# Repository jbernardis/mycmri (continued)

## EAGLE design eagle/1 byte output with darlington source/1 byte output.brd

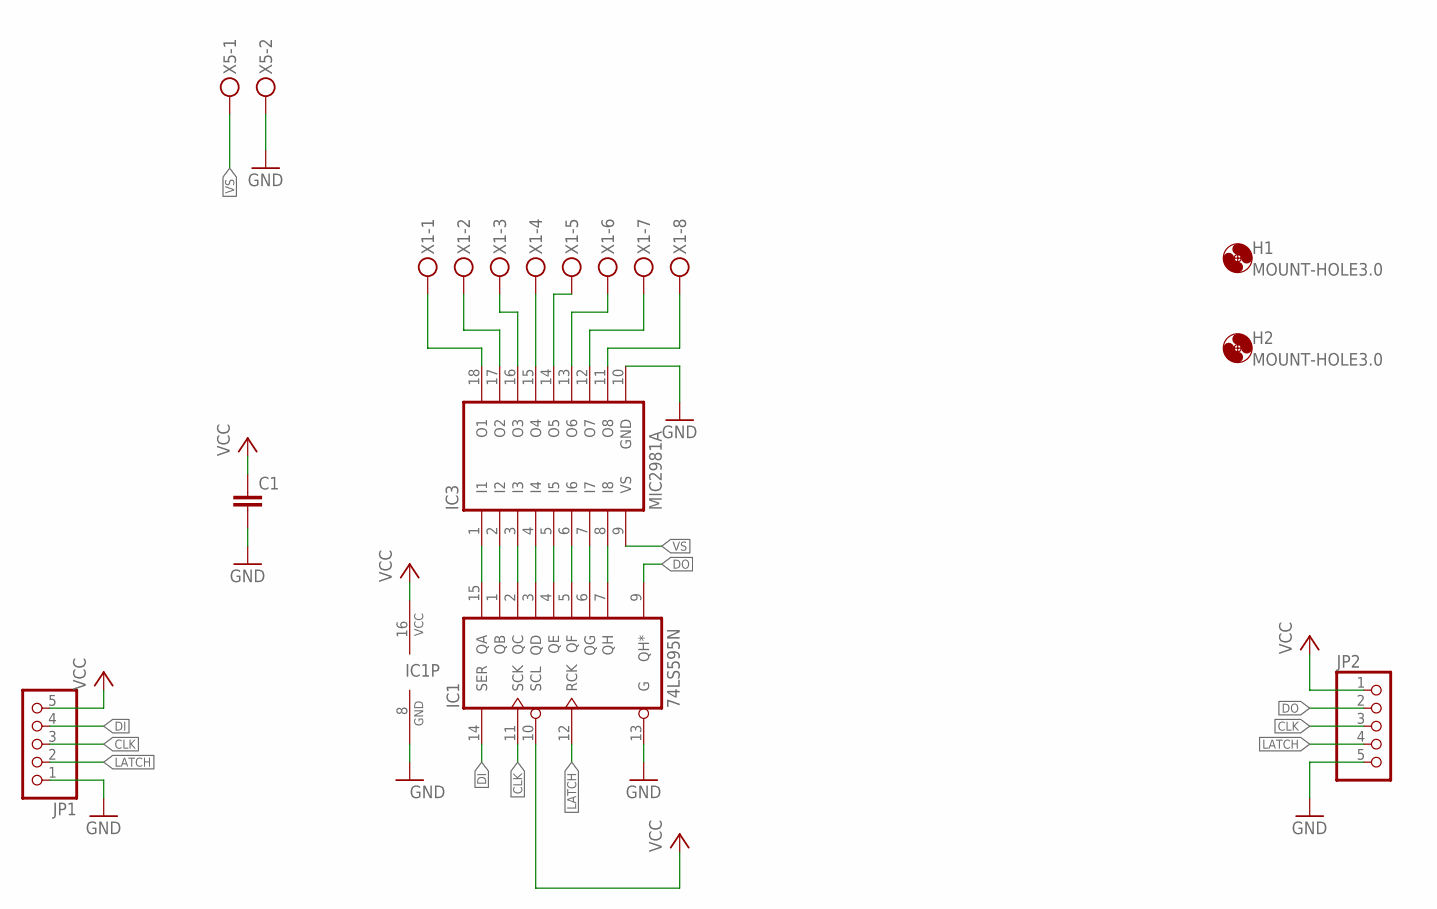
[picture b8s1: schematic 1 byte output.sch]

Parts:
C1: C-EU050-035X075; C050-035X075
H1, H2: MOUNT-HOLE3.0; 3,0
IC1: 74LS595N; DIL16
IC3: MIC2981A; DIL18
JP1, JP2: PINHD-1X5/90; 1X05/90
X1: MKDSN1,5/8-5,08
X5: MKDSN1,5/2-5,08

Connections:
CLK: IC1.11 (SCK), JP1.3, JP2.3
DI: IC1.14 (SER), JP1.4
DO: IC1.9 (QH*), JP2.2
GND: C1.2, IC1.8 (GND), IC1.13 (G), IC3.10 (GND), JP1.1, JP2.5, X5.2
LATCH: IC1.12 (RCK), JP1.2, JP2.4
unnamed: IC3.15 (O4), X1.4
unnamed: IC3.16 (O3), X1.3
unnamed: IC3.17 (O2), X1.2
unnamed: IC3.18 (O1), X1.1
unnamed: IC3.14 (O5), X1.5
unnamed: IC3.12 (O7), X1.7
unnamed: IC3.11 (O8), X1.8
unnamed: IC3.13 (O6), X1.6
unnamed: IC1.15 (QA), IC3.1 (I1)
unnamed: IC1.1 (QB), IC3.2 (I2)
unnamed: IC1.2 (QC), IC3.3 (I3)
unnamed: IC1.3 (QD), IC3.4 (I4)
unnamed: IC1.4 (QE), IC3.5 (I5)
unnamed: IC1.5 (QF), IC3.6 (I6)
unnamed: IC1.6 (QG), IC3.7 (I7)
unnamed: IC1.7 (QH), IC3.8 (I8)
VCC: C1.1, IC1.10 (SCL), IC1.16 (VCC), JP1.5, JP2.1
VS: IC3.9 (VS), X5.1

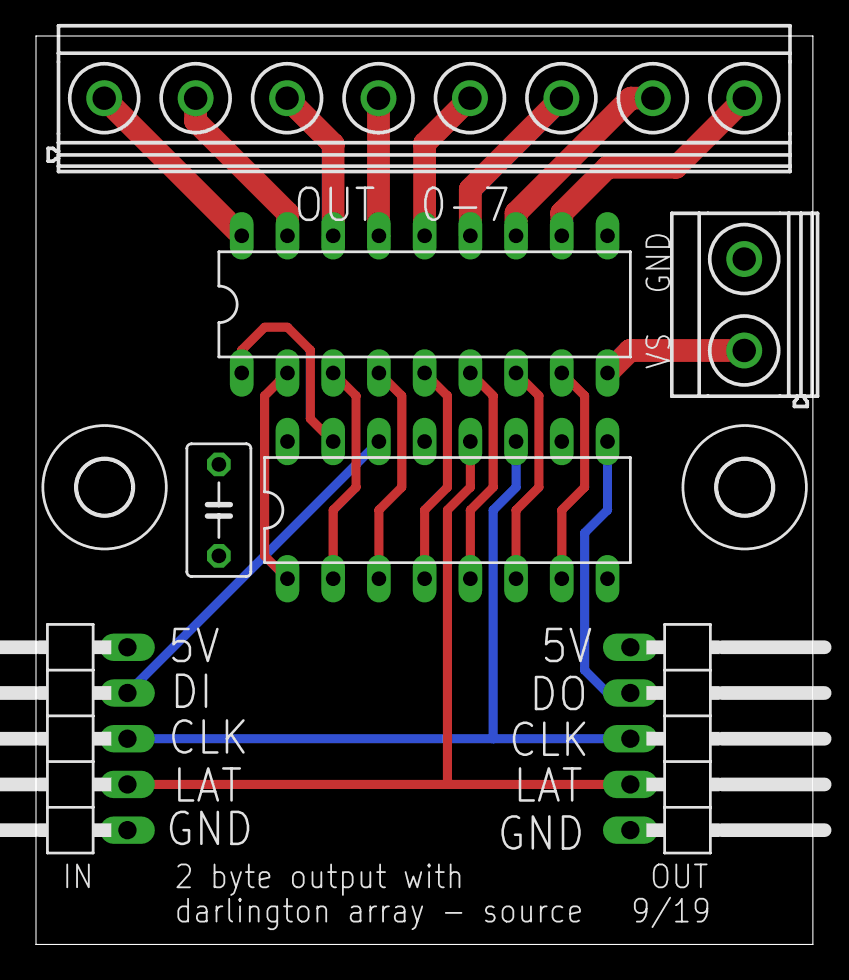
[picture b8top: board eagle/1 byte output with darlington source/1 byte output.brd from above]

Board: 2 copper layers, 43.2 x 50.5 mm, 9 parts (0 on the bottom side), 23 nets.

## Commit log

2019-07-11 initial commit of current eagle designs
2019-08-20 check in changes
2019-08-20 updated readme to reflect last commit
2019-08-24 corrected circuit for input board
2019-08-30 periodic check in - everything working so far with breadboards.
2019-09-19 periodic check-in
2019-10-11 periodic check in
2019-10-11 added pdf file of schematics and boards, removed button debounce and servo driver
2020-08-04 periodic checkin
2020-09-06 adding kicad designs - deleting unwanted eagle designd
2020-09-07 check in
2020-09-07 renaming inputboard to be all lowercase
2020-09-08 added probe information to arduino sketch
2020-09-09 periodic checkin - adding a node config tool
2020-09-11 removed timing statements
2020-09-11 added pihat, minor fix to rrmain
2020-09-13 changed representation of outputs from 0/1 to False/True
2020-09-14 changed input report to use true/false instead of 0/1
2020-09-14 adding nodetester utility
2020-09-16 added code for new dialog boxes - missing fromlast commit
2020-09-17 added final few reports/commands
2020-09-17 added logic to reverse bit order in inputs report
2020-09-18 restructured projects to be compatible with eclipse
2020-09-18 more compatibility changes
2020-09-18 Added tool tips. added shutdown button
2020-09-18 moved trigger tables and surrounding logic to separate project
2020-09-18 beefed up nodecfg to take command line arguments
2020-09-18 fixed protocol error - also fixed a type
2020-09-19 added a menu, restructured logic selecting node
2020-09-20 Added simple framing logic to socket protocol
2020-09-20 beefed up socket protocol - minor fix in nodetester.py
2020-09-20 removed a debugging statement
2020-09-21 added logging
2020-09-21 Beefed up error handling
2020-09-21 Added node active/inactive status to towers report
2020-09-21 fixed small bug
2020-09-21 renamed towers report to nodes report
2020-09-21 added logging to http interface
2020-09-23 reorganizing directories - added trigger host application
2020-09-23 still restructuring
2020-09-23 completing logic for trigger app
2020-09-23 clean up
2020-09-26 removed "jmri" from names
2020-10-18 changed node selection to not allow selection of an inactive node
2020-10-18 fixed logic when choosing a node
2020-10-28 added logic for new command: toggle turnout
2020-10-30 fixes
2020-11-10 added circuit for led flasher, added toggle command
2020-11-10 added logic to search up one directory for config file
2020-11-14 adding flags and registers constructs - still need to add to trigger
2020-11-17 implemented flags and registers in trigger
2021-03-24 reimplementation of rules - use pseudo python instead of json
2021-03-25 documented the http interface and the rules file format
2021-03-25 Added outputs as a matching criteria for triggers
2021-03-28 All triggers MUST have an input as a decision criteria
2021-04-29 periodic checkin - also adding c++ code for reimplementation of server
2021-05-11 added error checking and recovert
2021-05-11 rerouted several PCBs
2021-05-15 added logging using BOOST logging
2021-05-22 trigger re-write to work with new c server
2021-05-22 syncing systems
2021-05-27 fixed format or nodesrpt, updated http documentation
2021-06-05 debugging
2021-06-09 updating for running on raspberry pi
2021-07-27 added new command - pulse - to send a timed pulse to putputs
2021-07-28 added 2 byte mirrored output
2021-07-28 changes to tester to handle pulsed output
2021-07-28 testing revealed bugs - fixes
2021-07-28 Fixed display message routine to show buffer instead of msg
2021-07-29 added pulse length to outputs dialog - still needs position adjustment
2021-07-30 formated the outputs dialog details
2021-08-01 Fixed representation of pulse, corrected servo report syntax
2021-08-02 adding recovery from down/failed nodes
2021-08-02 logic to restart failed nodes - paced out node starts/restarts
2021-08-02 more changes for recovery logic
2021-08-04 added bus timeout to config file
2021-08-05 changes to error handling
2021-08-05 still working on error handling
2021-08-05 aligned columns in noderpr log entry
2021-08-06 added labels to inputs dlg, worked on dlg positioning
2022-03-22 added dcc sniffer, conversion to kicad 6
2022-03-22 reorganized dccsniffer as a python project
2022-03-22 added gitignore for dccsniffer
2022-05-01 updated dcc sniffer pcs, new arduino sketch for dcc server
2023-01-10 added switchdriver sketch
2024-11-11 long overdue update
